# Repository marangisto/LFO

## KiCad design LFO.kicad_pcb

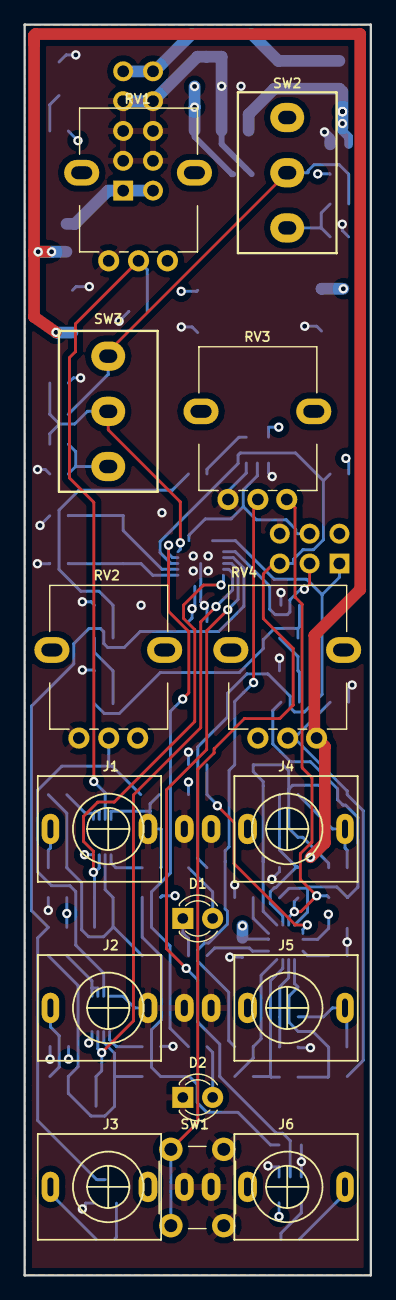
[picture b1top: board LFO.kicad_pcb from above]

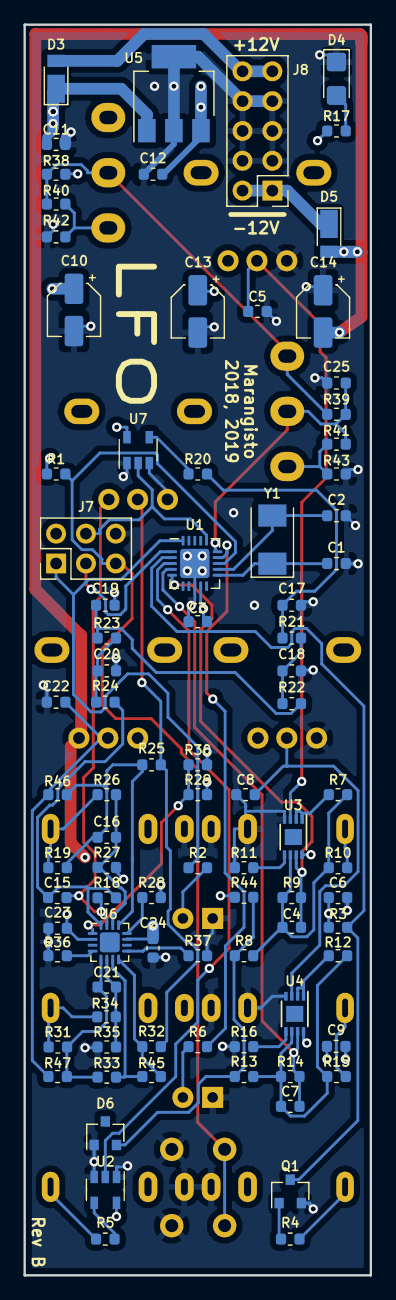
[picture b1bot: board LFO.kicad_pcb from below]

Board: 4 copper layers, 29.5 x 106.5 mm, 102 parts (87 on the bottom side), 60 nets.

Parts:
C1, C2: 22p; C_0603_1608Metric
C3, C5, C6, C8, C9, C11, C12, C22, C23, C24, C25: 100n; C_0603_1608Metric
C4, C7: 470p; C_0603_1608Metric
C10, C13, C14: 10u; CP_Elec_4x5.8
C15, C16, C21: 100p; C_0603_1608Metric
C17, C18, C19, C20: 47n; C_0603_1608Metric
D1, D2: LED; LED_D3.0mm
D3, D5: DFLR1400-7; D_PowerDI-123
D4: LED; LED_1206_3216Metric_Castellated
D6: LM4040DBZ-10; SOT-23
J1, J2, J3, J4, J5, J6: AudioJack2_SwitchT; PJ398SM
J7: Conn_02x03_Odd_Even; PinHeader_2x03_P2.54mm_Vertical
J8: Conn_02x05_Odd_Even; PinHeader_2x05_P2.54mm_Vertical
Q1: BC847; SOT-23
R1, R3, R30: 10k; R_0603_1608Metric
R2, R6, R17: 330; R_0603_1608Metric
R4, R7, R9, R12, R14, R15, R19, R25, R27, R31, R32, R33, R35, R45: 100k; R_0603_1608Metric
R5, R26, R34: 1k; R_0603_1608Metric
R8, R10, R13: 200k; R_0603_1608Metric
R11, R16, R28, R36, R37: 47k; R_0603_1608Metric
R18, R40: 68k; R_0603_1608Metric
R20, R21, R22, R23: 470; R_0603_1608Metric
R24, R41: 33k; R_0603_1608Metric
R29: 20k; R_0603_1608Metric
R38: 4k7; R_0603_1608Metric
R39: 15k; R_0603_1608Metric
R42: 3k3; R_0603_1608Metric
R43: 22k; R_0603_1608Metric
R44: 2k2; R_0603_1608Metric
R46, R47: 220k; R_0603_1608Metric
RV1, RV3: 100k; AlpsRK09K
RV2, RV4: 100k; R09M3KT
SW1: SW_Push; SW_PUSH_6mm_H9.5mm
SW2, SW3: SW_SPDT_MSM; SPDT
U1: ATtiny84-20MU; QFN-20-1EP_4x4mm_P0.5mm_EP2.5x2.5mm
U2, U7: 74AHCT1G125; SOT-23-5
U3, U4: MCP6002-xMS; DFN-8-1EP_3x2mm_P0.5mm_EP1.36x1.46mm
U5: L7805; SOT-223-3_TabPin2
U6: LM324QT; QFN-16-1EP_3x3mm_P0.5mm_EP1.7x1.7mm
Y1: 20MHz; Crystal_SMD_Abracon_ABM3-2Pin_5.0x3.2mm

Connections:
+5V: C3.1, C6.1, C9.1, C12.1, C13.1, J3.TN, J7.2, R1.1, R3.1, R17.1, R29.2, R38.1, RV1.1, RV2.1, SW2.3, U1.9, U2.5, U3.8, U4.8, U5.3, U7.5
+12V: C10.1, C11.1, C23.1, D3.1, RV4.3, U5.1, U6.2
-12V: C14.2, C24.2, D5.2, R44.1, RV4.1, U6.11
/CVIn05.sch/In: J2.T, R15.1
/CVIn55/In: J1.T, R10.1
/DigitalIn/In: J3.T, R4.1
/DigitalOut/Out: J6.T, R5.1
/OutputStage/Inv: J5.T, R31.1, R34.1
/OutputStage/Out: J4.T, R19.1, R26.1
FREQ: C4.1, R9.1, U1.5, U3.7
GND: C1.1, C2.1, C3.2, C5.2, C6.2, C8.2, C9.2, C10.2, C11.2, C12.2, C13.2, C14.1, C17.2, C18.2, C19.2, C20.2, C22.2, C23.2, C24.1, C25.2, D1.1, D2.1, D4.1, D6.1, J1.S, J1.TN, J2.S, J2.TN, J3.S, J4.S, J5.S, J6.S, J7.6, J8.3, J8.4, J8.5, J8.6, J8.7, J8.8, Q1.2, R11.2, R16.2, R27.2, R28.1, R30.1, R35.2, R36.1, R37.1, R42.2, R43.2, RV1.3, RV2.3, RV3.3, SW1.2, U1.8, U1.21, U2.1, U2.3, U3.4, U4.4, U5.2, U7.1, U7.3
LED1: J7.1, R2.1, U1.20
LED2: R6.1, U1.14
MOSI: J7.4, U1.16, U7.2
unnamed: C1.2, U1.11, Y1.1
unnamed: C2.2, U1.12, Y1.2
unnamed: C4.2, R7.2, R8.2, R9.2, R10.2, U3.6
unnamed: C5.1, RV1.2, U3.3
unnamed: C7.2, R12.2, R13.2, R14.2, R15.2, U4.6
unnamed: C8.1, RV2.2, U4.3
unnamed: C15.1, R18.1, RV3.1, U6.15
unnamed: C15.2, R18.2, R24.1, U6.16
unnamed: C16.1, R26.2, R27.1, U6.14
unnamed: C16.2, R19.2, R25.2, R46.2, U6.13
unnamed: C17.1, R20.1, R21.2
unnamed: C18.1, R21.1, R22.2
unnamed: C19.1, R22.1, R23.2
unnamed: C20.1, R23.1, R24.2
unnamed: C21.1, R34.2, R35.1, U6.6
unnamed: C21.2, R31.2, R33.2, R47.2, U6.5
unnamed: C22.1, R46.1, R47.1, RV4.2
unnamed: D1.2, R2.2
unnamed: D2.2, R6.2
unnamed: D3.2, J8.9, J8.10
unnamed: D4.2, R17.2
unnamed: D5.1, J8.1, J8.2
unnamed: Q1.1, R4.2
unnamed: R5.2, U2.4
unnamed: R7.1, U3.1, U3.2
unnamed: R11.1, U3.5
unnamed: R12.1, U4.1, U4.2
unnamed: R16.1, U4.5
unnamed: R25.1, R32.2, RV3.2
unnamed: R28.2, U6.12
unnamed: R29.1, R30.2, U6.1
unnamed: R32.1, R45.2, U6.8
unnamed: R33.1, R45.1, U6.7
unnamed: R36.2, U6.4
unnamed: R37.2, U6.9
unnamed: R38.2, R39.1, R40.1, SW2.2, SW3.3
unnamed: R40.2, R42.1, SW2.1
unnamed: R41.2, R43.1, SW3.1
OUT: R20.2, U7.4
PWM: C7.1, R14.1, U1.4, U4.7
RESET: J7.5, R1.2, SW1.1, U1.13
SCK: J7.3, U1.1
SPDTS: C25.1, R39.2, R41.1, SW3.2, U1.15
SYNC: Q1.3, R3.2, U1.2
TRIG: U1.3, U2.2
VRef-10: D6.2, R8.1, R13.1, R44.2

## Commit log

2018-12-26 Initial LFO project.
2018-12-27 Draft schematic design.
2018-12-29 Added decoder function (with zero secondary current draw assumption).
2018-12-29 Decode with complete circuit.
2018-12-29 Output stage and switches.
2018-12-29 Added missing cap on switch circuit.
2018-12-29 Added screenshot of decoder schema.
2018-12-30 LED2 assignment and keep high sync when unconnected.
2018-12-30 Footprints and adjustments.
2018-12-30 Added local footprint library.
2018-12-30 Upgraded to KiCad 5.02 and set footprints.
2018-12-30 Board geometry.
2018-12-30 Initial placement.
2018-12-30 Updated footprint library.
2018-12-30 First complete placement.
2018-12-30 Better orientation of op-amp.
2018-12-30 Manually routed power.
2018-12-30 Autorouted signals and manual pours and adjustments.
2018-12-31 Added keepouts for jacks.
2018-12-31 Front silk-screen.
2018-12-31 Back silk-screen.
2018-12-31 Branding.
2018-12-31 Added missing files.
2018-12-31 Some renderings.
2018-12-31 More renderings.
2018-12-31 Added Gerbers.
2018-12-31 Added BOM.
2019-02-19 Added sheet for switch decoder table.
2019-03-02 Updated calibrated spdts levels.
2019-03-03 Inital symbol for LM324QT.
2019-03-03 Corrected pin-assignments on new symbol.
2019-03-03 Added local symbol library.
2019-03-03 Use correct symbol for LM324QT.
2019-03-03 Use symbol for path to local library.
2019-03-09 Added sheet to compute frequency tables for firmare.
2019-03-10 Redesigned output stage for proper handling of offset.
2019-03-10 Minor adjustments to output stage.
2019-03-10 Added some scope shots.
2019-03-23 Upgraded to KiCad 5.1 and added programming jumper.
2019-03-23 Moved LED1 to PA5 (PWM capable) and LED2 to PB2 for separate control.
2019-03-24 Use new package for LM324QT.
2019-03-24 Added footprint and 3-d model for R09M3KT pots.
2019-03-24 Added 3D model for Davies-900 knob.
2019-03-25 Added revison-b layout rendering.
2019-03-26 Added buffer on PWM out and changed footprints for MCP6002 and 7805 for smaller size.
2019-03-26 New drawing and edgecuts for new layout.
2019-04-01 Initial placement and power.
2019-04-02 Some minor placement adjustments.
2019-04-02 Removed old gerbers.
2019-04-03 Completed 4-layer routing.
2019-04-08 Autorouted 2-layer version but no power routing done.
2019-04-14 Revert "Autorouted 2-layer version but no power routing done."
    This reverts commit d698285758b8106e3bcfe68091c579182fce5db9.
2019-04-14 Added top and bottom pours.
2019-04-14 Moved a resistor for better routing.
2019-04-14 Ground vias for MCU.
2019-04-14 Double power vias.
2019-04-14 Updated gerbers for rev B.
2019-05-01 Added step model for crystal.
2019-05-01 Added step model for whole module.
2019-05-05 Moved firmware from AVR project.
2019-05-05 Led2 to follow trigger output.
2019-05-05 Led-1 on pwm channel b.
2019-05-05 Led1 pwm is not inverted.
2019-05-05 Reset on range changes to avoid lock-up on slow speed.
2019-05-05 Corrected direction for led1.
2019-05-05 Added sync interrupt reset.
